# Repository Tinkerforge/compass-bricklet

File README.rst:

Compass Bricklet
================

This repository contains the firmware source code and the hardware design
files. The documentation generator configs can be found at
https://github.com/Tinkerforge/generators

Repository Content
------------------

software/:
 * examples/: Examples for all supported languages
 * build/: Compiled files
 * src/: Source code of firmware
 * Makefile: Makefile to build project

hardware/:
 * Contains KiCad project files and additionally schematics as PDF

datasheets/:
 * Contains datasheets for sensors and complex ICs that are used

Hardware
--------

The hardware is designed with the open source EDA Suite KiCad
(http://www.kicad.org). Before you are able to open the files,
you have to install the Tinkerforge kicad-libraries
(https://github.com/Tinkerforge/kicad-libraries). You can either clone
them directly in hardware/ or clone them in a separate folder and
symlink them into hardware/
(ln -s kicad_path/kicad-libraries project_path/hardware). After that you
can open the .pro file in hardware/ with KiCad and from there view and
modify the schematics and the PCB layout.

Software
--------

If you want to do your own Brick/Bricklet firmware development we highly
recommend that you use our build environment setup script and read the
tutorial (https://www.tinkerforge.com/en/doc/Tutorials/Tutorial_Build_Environment/Tutorial.html).

To compile the C code we recommend you to install the newest GNU Arm Embedded
Toolchain (https://launchpad.net/gcc-arm-embedded/+download).
You also need to install bricklib2 (https://github.com/Tinkerforge/bricklib2).

You can either clone it directly in software/src/ or clone it in a
separate folder and symlink it into software/src/
(ln -s bricklib_path/bricklib2 project_path/software/src/). Finally make sure to
have CMake installed (http://www.cmake.org/cmake/resources/software.html).

After that you can build the firmware by invoking make in software/.
The firmware (.zbin) can then be found in software/build/ and uploaded
with brickv (click button "Flashing" on start screen).

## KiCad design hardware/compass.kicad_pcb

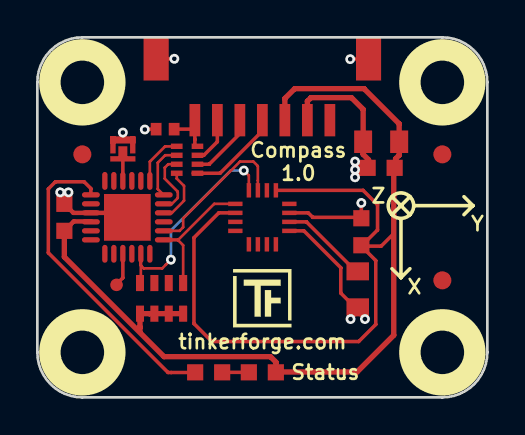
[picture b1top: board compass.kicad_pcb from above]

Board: 2 copper layers, 25.0 x 20.0 mm, 24 parts (2 on the bottom side), 18 nets.

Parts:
C1: 100nF; C0603F
C2, C5: 1uF; C0603F
C3: 220pF; C0402F
C4, C6: 10uF; C0805
D1: blue; D0603F
Fiducial_Mark: VAL**; Fiducial_Mark
Fiducial_Mark#2, Fiducial_Mark#3: VAL**; Fiducial_Mark
P1: CON-SENSOR2
P2: DEBUG; DEBUG_PAD
P3: BOOT; SolderJumper
R1: 1k; R0603F
RP1: 82; 4X0402
RP2: 2k2; 4X0603
U1: XMC1300; QFN24-4x4mm-0.5mm
U2: MMC5883MA; LGA16-3x3_Compass
U3, U4, U5, U6: DRILL; DRILL_NP
VAL: WEEE_7mm
VAL#2: CE_5mm

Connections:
GND: C1.2, C2.1, C3.2, C4.2, C5.2, C6.2, P1.2, P1.EP, P3.1, U1.9, U1.EXP, U2.9, U2.11
INTERRUPT: U1.20, U2.15
unnamed: C3.1, P1.7, RP1.4
unnamed: C6.1, U2.10
unnamed: D1.2, R1.2
unnamed: P1.4, RP1.1
unnamed: P1.5, RP1.2
unnamed: P1.6, RP1.3
unnamed: P2.1, U1.15
unnamed: P3.2, U1.4
unnamed: R1.1, U1.7
S-CLK: RP1.7, U1.23
S-CS: RP1.8, U1.22
S-MISO: RP1.5, U1.1
S-MOSI: RP1.6, U1.24
SCL: RP2.8, U1.19, U2.1
SDA: RP2.5, U1.17, U2.16
VCC: C1.1, C2.2, C4.1, C5.1, D1.1, P1.3, RP2.1, RP2.2, RP2.3, RP2.4, U1.10, U2.2, U2.13

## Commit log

2019-02-12 initial push, .gitignore, readme, kicadproject, schematic
2019-02-12 changed schematic, connect MMC
2019-02-13 first pcb design
2019-02-13 added silkscreen
2019-03-11 changed footprint of MMC to LGA16
2019-04-04 updated footprint to LGA-16-3x3_Compass, moved some caps for better screw clearance
2019-04-23 Add auto-generated firmware stub
2019-04-23 Add basic MMC5883MA driver configuration and setup
2019-04-25 Add driver and API implementation for MMC5883MA
2019-05-02 changed co-processor to xmc1300
2019-05-03 Add auto-generated examples
2019-08-14 Turn logging off
2019-08-14 Add changelog entry for inital version
2019-08-15 add lda16 3d model for sensor
2019-08-15 add 3d data
2019-08-15 Rename multiplier to gain.
2019-08-15 add schematic
2019-08-22 c: Adapt to bindings changes
2019-08-22 rust: Style cleanup
2019-08-22 Remove development marker
2019-08-23 Fix multiplier/gain mixup
2020-01-13 examples: Use python3 input instead of python2 raw_input.
2020-01-13 examples: mqtt: Remove trailing whitespace.
2020-08-19 Add uc examples.
2020-08-25 uc: Fix whitespace
2020-08-27 uc: Fix warnings.
2020-09-02 uc: Add example driver note.
2020-10-16 uc: Fix divisor type.
2021-10-25 Update KiCad link
    https://www.kicad.org/blog/2021/10/Avoid-links-to-former-kicad-domain/
2022-04-19 examples: uc: Rename TF_HalContext to TF_HAL.
2022-04-27 uc: Adapt to bindings changes
2022-07-06 Add license files.
2025-10-04 Fix compatibility with new Docker build image (GCC 14.2.1)

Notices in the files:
hardware/compass.kicad_pcb:
Licensed under CERN OHL v.1.1
Copyright (©) 2019, T.Schneidermann
